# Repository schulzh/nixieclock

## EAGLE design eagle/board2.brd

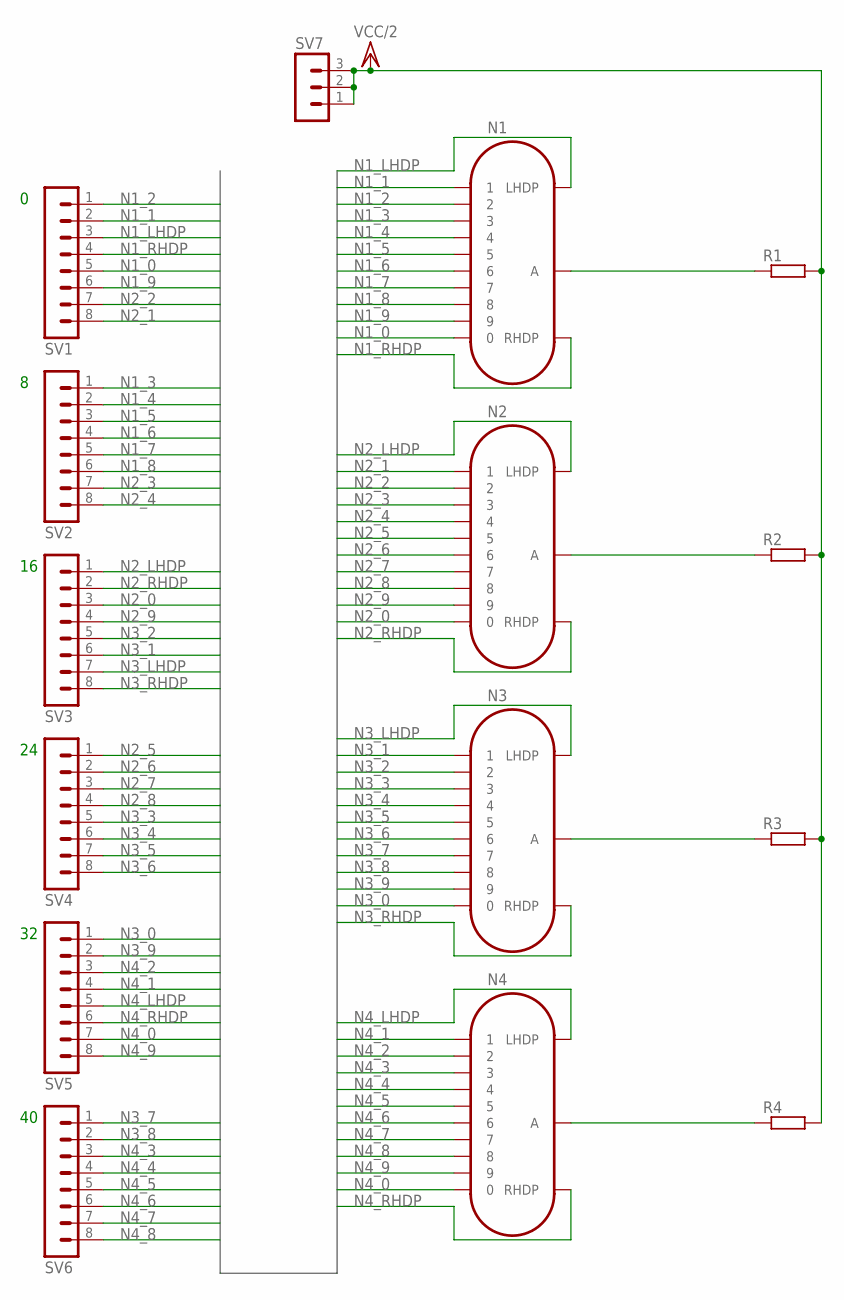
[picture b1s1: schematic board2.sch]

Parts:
N1, N2, N3, N4: IN-14
R1, R2, R3, R4: R-EU_0207/7; 0207/7
SV1, SV2, SV3, SV4, SV5, SV6: MA08-1
SV7: MA03-1

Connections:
N1_0: N1.0, SV1.5
N1_1: N1.1, SV1.2
N1_2: N1.2, SV1.1
N1_3: N1.3, SV2.1
N1_4: N1.4, SV2.2
N1_5: N1.5, SV2.3
N1_6: N1.6, SV2.4
N1_7: N1.7, SV2.5
N1_8: N1.8, SV2.6
N1_9: N1.9, SV1.6
N1_LHDP: N1.LHDP, SV1.3
N1_RHDP: N1.RHDP, SV1.4
N2_0: N2.0, SV3.3
N2_1: N2.1, SV1.8
N2_2: N2.2, SV1.7
N2_3: N2.3, SV2.7
N2_4: N2.4, SV2.8
N2_5: N2.5, SV4.1
N2_6: N2.6, SV4.2
N2_7: N2.7, SV4.3
N2_8: N2.8, SV4.4
N2_9: N2.9, SV3.4
N2_LHDP: N2.LHDP, SV3.1
N2_RHDP: N2.RHDP, SV3.2
N3_0: N3.0, SV5.1
N3_1: N3.1, SV3.6
N3_2: N3.2, SV3.5
N3_3: N3.3, SV4.5
N3_4: N3.4, SV4.6
N3_5: N3.5, SV4.7
N3_6: N3.6, SV4.8
N3_7: N3.7, SV6.1
N3_8: N3.8, SV6.2
N3_9: N3.9, SV5.2
N3_LHDP: N3.LHDP, SV3.7
N3_RHDP: N3.RHDP, SV3.8
N4_0: N4.0, SV5.7
N4_1: N4.1, SV5.4
N4_2: N4.2, SV5.3
N4_3: N4.3, SV6.3
N4_4: N4.4, SV6.4
N4_5: N4.5, SV6.5
N4_6: N4.6, SV6.6
N4_7: N4.7, SV6.7
N4_8: N4.8, SV6.8
N4_9: N4.9, SV5.8
N4_LHDP: N4.LHDP, SV5.5
N4_RHDP: N4.RHDP, SV5.6
unnamed: N1.A, R1.1
unnamed: N2.A, R2.1
unnamed: N3.A, R3.1
unnamed: N4.A, R4.1
VCC/2: R1.2, R2.2, R3.2, R4.2, SV7.1, SV7.2, SV7.3

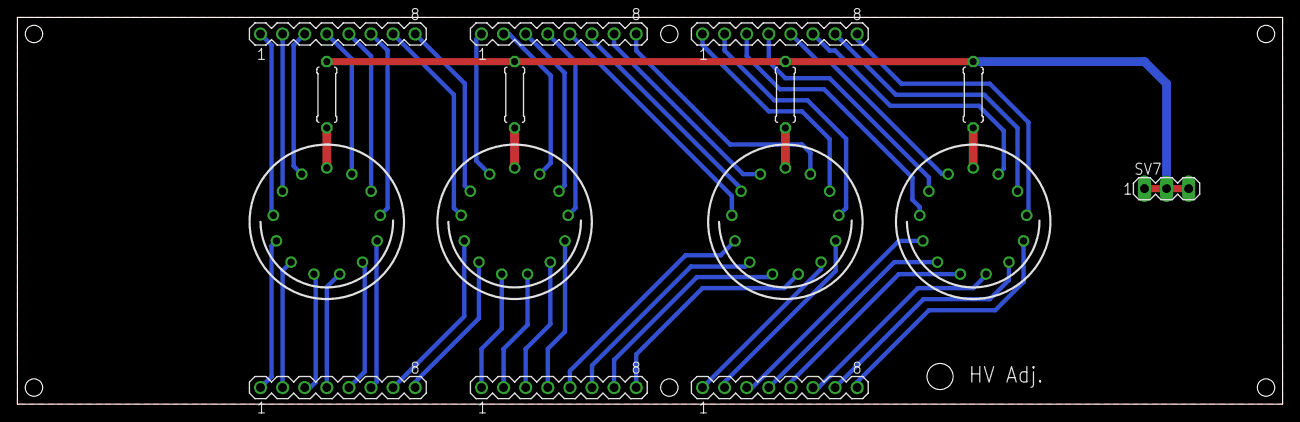
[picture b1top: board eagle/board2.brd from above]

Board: 2 copper layers, 145.4 x 44.5 mm, 15 parts (0 on the bottom side), 53 nets.

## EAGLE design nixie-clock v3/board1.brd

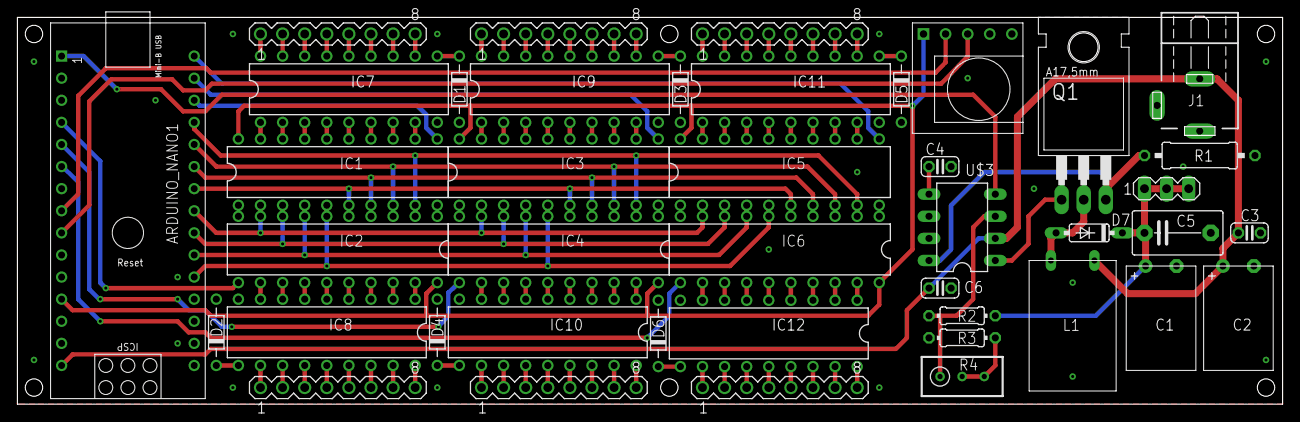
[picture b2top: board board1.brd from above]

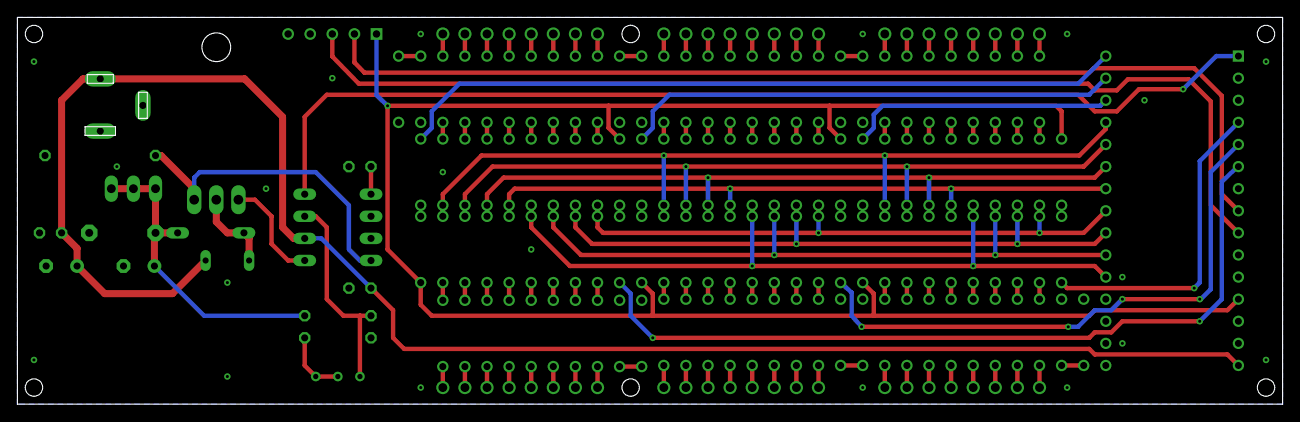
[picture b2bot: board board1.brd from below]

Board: 2 copper layers, 145.4 x 44.5 mm, 42 parts (2 on the bottom side), 129 nets.

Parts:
ARDUINO_NANO1: ARDUINO_NANO
C1, C2: E3,5-8
C3, C4, C6: C025-024X044
C5: C7.5B5
D1, D2, D3, D4, D5, D6: D-7.5
D7: DO35-7
IC1, IC2, IC3, IC4, IC5, IC6: 74HC573N; DIL20
IC7, IC8, IC9, IC10, IC11, IC12: DIL18
J1: NEB21R
L1: BS11
Q1: IRF620; TO220
R1: 0309/12
R2: 1M5; 0204/7
R3: 10k; 0204/7
R4: 5k; RTRIM3296W
SV1, SV2, SV3, SV4, SV5, SV6: MA08-1
SV7: MA03-1
U$1: DS3231_MINI_MODULE
U$3: MAX1771; DIL08

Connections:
+12V: ARDUINO_NANO1.15, C2.+, C3.1, C6.1, J1.3, L1.1, U$3.2
CS1: ARDUINO_NANO1.28, IC1.11
CS2: ARDUINO_NANO1.4, IC2.11
CS3: ARDUINO_NANO1.29, IC3.11
CS4: ARDUINO_NANO1.5, IC4.11
CS5: ARDUINO_NANO1.30, IC5.11
CS6: ARDUINO_NANO1.6, IC6.11
D1: ARDUINO_NANO1.23, IC1.2, IC2.9, IC3.2, IC4.9, IC5.2, IC6.9
D2: ARDUINO_NANO1.22, IC1.3, IC2.8, IC3.3, IC4.8, IC5.3, IC6.8
D3: ARDUINO_NANO1.21, IC1.4, IC2.7, IC3.4, IC4.7, IC5.4, IC6.7
D4: ARDUINO_NANO1.20, IC1.5, IC2.6, IC3.5, IC4.6, IC5.5, IC6.6
D5: ARDUINO_NANO1.24, IC1.6, IC2.5, IC3.6, IC4.5, IC5.6, IC6.5
D6: ARDUINO_NANO1.25, IC1.7, IC2.4, IC3.7, IC4.4, IC5.7, IC6.4
D7: ARDUINO_NANO1.26, IC1.8, IC2.3, IC3.8, IC4.3, IC5.8, IC6.3
D8: ARDUINO_NANO1.27, IC1.9, IC2.2, IC3.9, IC4.2, IC5.9, IC6.2
GND: ARDUINO_NANO1.14, ARDUINO_NANO1.19, C1.-, C2.-, C3.2, C4.2, C5.2, C6.2, D1.A, D2.A, D3.A, D4.A, D5.A, D6.A, IC1.1, IC1.10, IC2.1, IC2.10, IC3.1, IC3.10, IC4.1, IC4.10, IC5.1, IC5.10, IC6.1, IC6.10, IC7.9, IC8.9, IC9.9, IC10.9, IC11.9, IC12.9, J1.1, J1.2, R1.1, R3.1, U$1.5, U$3.6, U$3.7
HV: C1.+, C5.1, D7.C, R2.2, SV7.1, SV7.2, SV7.3
unnamed: IC2.19, IC8.1
unnamed: IC2.18, IC8.2
unnamed: IC2.17, IC8.3
unnamed: IC2.16, IC8.4
unnamed: IC2.15, IC8.5
unnamed: IC2.14, IC8.6
unnamed: IC2.13, IC8.7
unnamed: IC2.12, IC8.8
unnamed: IC1.19, IC7.1
unnamed: IC1.18, IC7.2
unnamed: IC1.17, IC7.3
unnamed: IC1.16, IC7.4
unnamed: IC1.15, IC7.5
unnamed: IC1.14, IC7.6
unnamed: IC1.13, IC7.7
unnamed: IC1.12, IC7.8
unnamed: IC3.19, IC9.1
unnamed: IC3.18, IC9.2
unnamed: IC3.17, IC9.3
unnamed: IC3.16, IC9.4
unnamed: IC3.15, IC9.5
unnamed: IC3.14, IC9.6
unnamed: IC3.13, IC9.7
unnamed: IC3.12, IC9.8
unnamed: IC4.19, IC10.1
unnamed: IC4.18, IC10.2
unnamed: IC4.17, IC10.3
unnamed: IC4.16, IC10.4
unnamed: IC4.15, IC10.5
unnamed: IC4.14, IC10.6
unnamed: IC4.13, IC10.7
unnamed: IC4.12, IC10.8
unnamed: IC5.19, IC11.1
unnamed: IC5.18, IC11.2
unnamed: IC5.17, IC11.3
unnamed: IC5.16, IC11.4
unnamed: IC5.15, IC11.5
unnamed: IC5.14, IC11.6
unnamed: IC5.13, IC11.7
unnamed: IC5.12, IC11.8
unnamed: IC6.19, IC12.1
unnamed: IC6.18, IC12.2
unnamed: IC6.17, IC12.3
unnamed: IC6.16, IC12.4
unnamed: IC6.15, IC12.5
unnamed: IC6.14, IC12.6
unnamed: IC6.13, IC12.7
unnamed: IC6.12, IC12.8
unnamed: IC7.18, SV1.1
unnamed: IC7.17, SV1.2
unnamed: IC7.16, SV1.3
unnamed: IC7.15, SV1.4
unnamed: IC7.14, SV1.5
unnamed: IC7.13, SV1.6
unnamed: IC7.12, SV1.7
unnamed: IC7.11, SV1.8
unnamed: IC8.18, SV2.8
unnamed: IC8.17, SV2.7
unnamed: IC8.16, SV2.6
unnamed: IC8.15, SV2.5
unnamed: IC8.14, SV2.4
unnamed: IC8.13, SV2.3
unnamed: IC8.12, SV2.2
unnamed: IC8.11, SV2.1
unnamed: IC9.18, SV3.1
unnamed: IC9.17, SV3.2
unnamed: IC9.16, SV3.3
unnamed: IC9.15, SV3.4
unnamed: IC9.14, SV3.5
unnamed: IC9.13, SV3.6
unnamed: IC9.12, SV3.7
unnamed: IC9.11, SV3.8
unnamed: IC10.18, SV4.8
unnamed: IC10.17, SV4.7
unnamed: IC10.16, SV4.6
unnamed: IC10.15, SV4.5
unnamed: IC10.14, SV4.4
unnamed: IC10.13, SV4.3
unnamed: IC10.12, SV4.2
unnamed: IC10.11, SV4.1
unnamed: IC11.18, SV5.1
unnamed: IC11.17, SV5.2
unnamed: IC11.16, SV5.3
unnamed: IC11.15, SV5.4
unnamed: IC11.14, SV5.5
unnamed: IC11.13, SV5.6
unnamed: IC11.12, SV5.7
unnamed: IC11.11, SV5.8
unnamed: IC12.18, SV6.8
unnamed: IC12.17, SV6.7
unnamed: IC12.16, SV6.6
unnamed: IC12.15, SV6.5
unnamed: IC12.14, SV6.4
unnamed: IC12.13, SV6.3
unnamed: IC12.12, SV6.2
unnamed: IC12.11, SV6.1
unnamed: ARDUINO_NANO1.8, U$1.2
unnamed: D1.C, IC7.10
unnamed: ARDUINO_NANO1.9, U$1.3
unnamed: D2.C, IC8.10
unnamed: D3.C, IC9.10
unnamed: D4.C, IC10.10
unnamed: C4.1, U$3.5
unnamed: D5.C, IC11.10
unnamed: Q1.1, U$3.1
unnamed: D6.C, IC12.10
unnamed: D7.A, L1.2, Q1.2
unnamed: Q1.3, R1.2, U$3.8
unnamed: R2.1, R4.1, U$3.3
unnamed: R3.2, R4.2, R4.3
SHDN: ARDUINO_NANO1.1, U$3.4
VCC: ARDUINO_NANO1.12, IC1.20, IC2.20, IC3.20, IC4.20, IC5.20, IC6.20, U$1.1

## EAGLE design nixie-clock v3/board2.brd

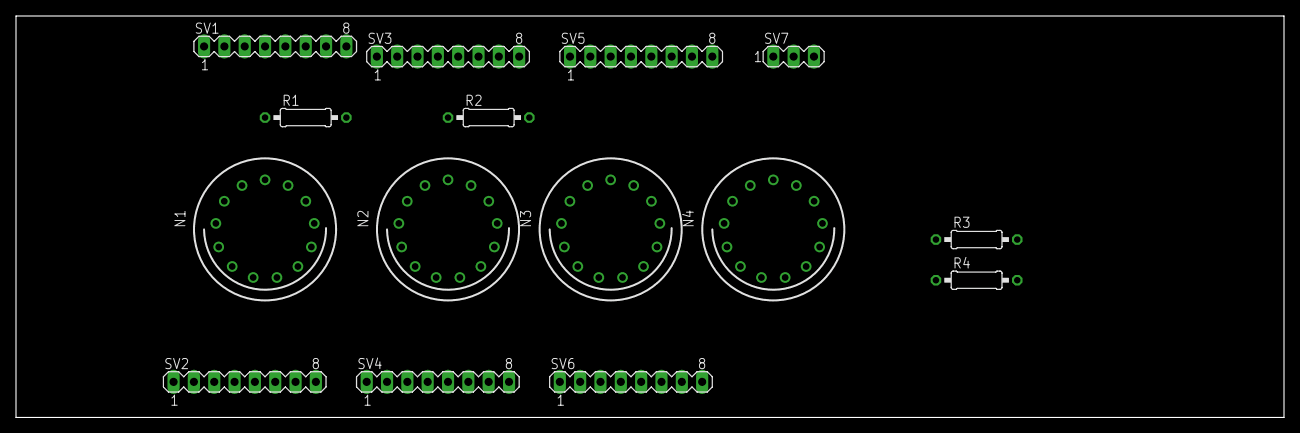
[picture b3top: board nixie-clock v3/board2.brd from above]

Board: 2 copper layers, 158.4 x 50.2 mm, 15 parts (0 on the bottom side), 53 nets, no tracks yet.

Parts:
N1, N2, N3, N4: IN-14
R1, R2, R3, R4: 0207/10
SV1, SV2, SV3, SV4, SV5, SV6: MA08-1
SV7: MA03-1

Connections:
N1_0: N1.0, SV1.2
N1_1: N1.1, SV1.5
N1_2: N1.2, SV1.6
N1_3: N1.3, SV2.6
N1_4: N1.4, SV2.5
N1_5: N1.5, SV2.4
N1_6: N1.6, SV2.3
N1_7: N1.7, SV2.2
N1_8: N1.8, SV2.1
N1_9: N1.9, SV1.1
N1_LHDP: N1.LHDP, SV1.3
N1_RHDP: N1.RHDP, SV1.4
N2_0: N2.0, SV1.8
N2_1: N2.1, SV3.3
N2_2: N2.2, SV3.4
N2_3: N2.3, SV4.4
N2_4: N2.4, SV4.3
N2_5: N2.5, SV4.2
N2_6: N2.6, SV4.1
N2_7: N2.7, SV2.8
N2_8: N2.8, SV2.7
N2_9: N2.9, SV1.7
N2_LHDP: N2.LHDP, SV3.1
N2_RHDP: N2.RHDP, SV3.2
N3_0: N3.0, SV3.6
N3_1: N3.1, SV5.1
N3_2: N3.2, SV5.2
N3_3: N3.3, SV6.2
N3_4: N3.4, SV6.1
N3_5: N3.5, SV4.8
N3_6: N3.6, SV4.7
N3_7: N3.7, SV4.6
N3_8: N3.8, SV4.5
N3_9: N3.9, SV3.5
N3_LHDP: N3.LHDP, SV3.7
N3_RHDP: N3.RHDP, SV3.8
N4_0: N4.0, SV5.4
N4_1: N4.1, SV5.7
N4_2: N4.2, SV5.8
N4_3: N4.3, SV6.8
N4_4: N4.4, SV6.7
N4_5: N4.5, SV6.6
N4_6: N4.6, SV6.5
N4_7: N4.7, SV6.4
N4_8: N4.8, SV6.3
N4_9: N4.9, SV5.3
N4_LHDP: N4.LHDP, SV5.5
N4_RHDP: N4.RHDP, SV5.6
unnamed: N1.A, R1.1
unnamed: N2.A, R2.1
unnamed: N3.A, R3.1
unnamed: N4.A, R4.1
VCC/2: R1.2, R2.2, R3.2, R4.2, SV7.1, SV7.2, SV7.3

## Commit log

2019-07-20 initial draft
2020-10-06 lots of board progress
2021-01-01 final pcbs, new code
2021-01-01 remove unnecessary files
2025-05-01 Add esphome component
2025-09-01 fix compile error
